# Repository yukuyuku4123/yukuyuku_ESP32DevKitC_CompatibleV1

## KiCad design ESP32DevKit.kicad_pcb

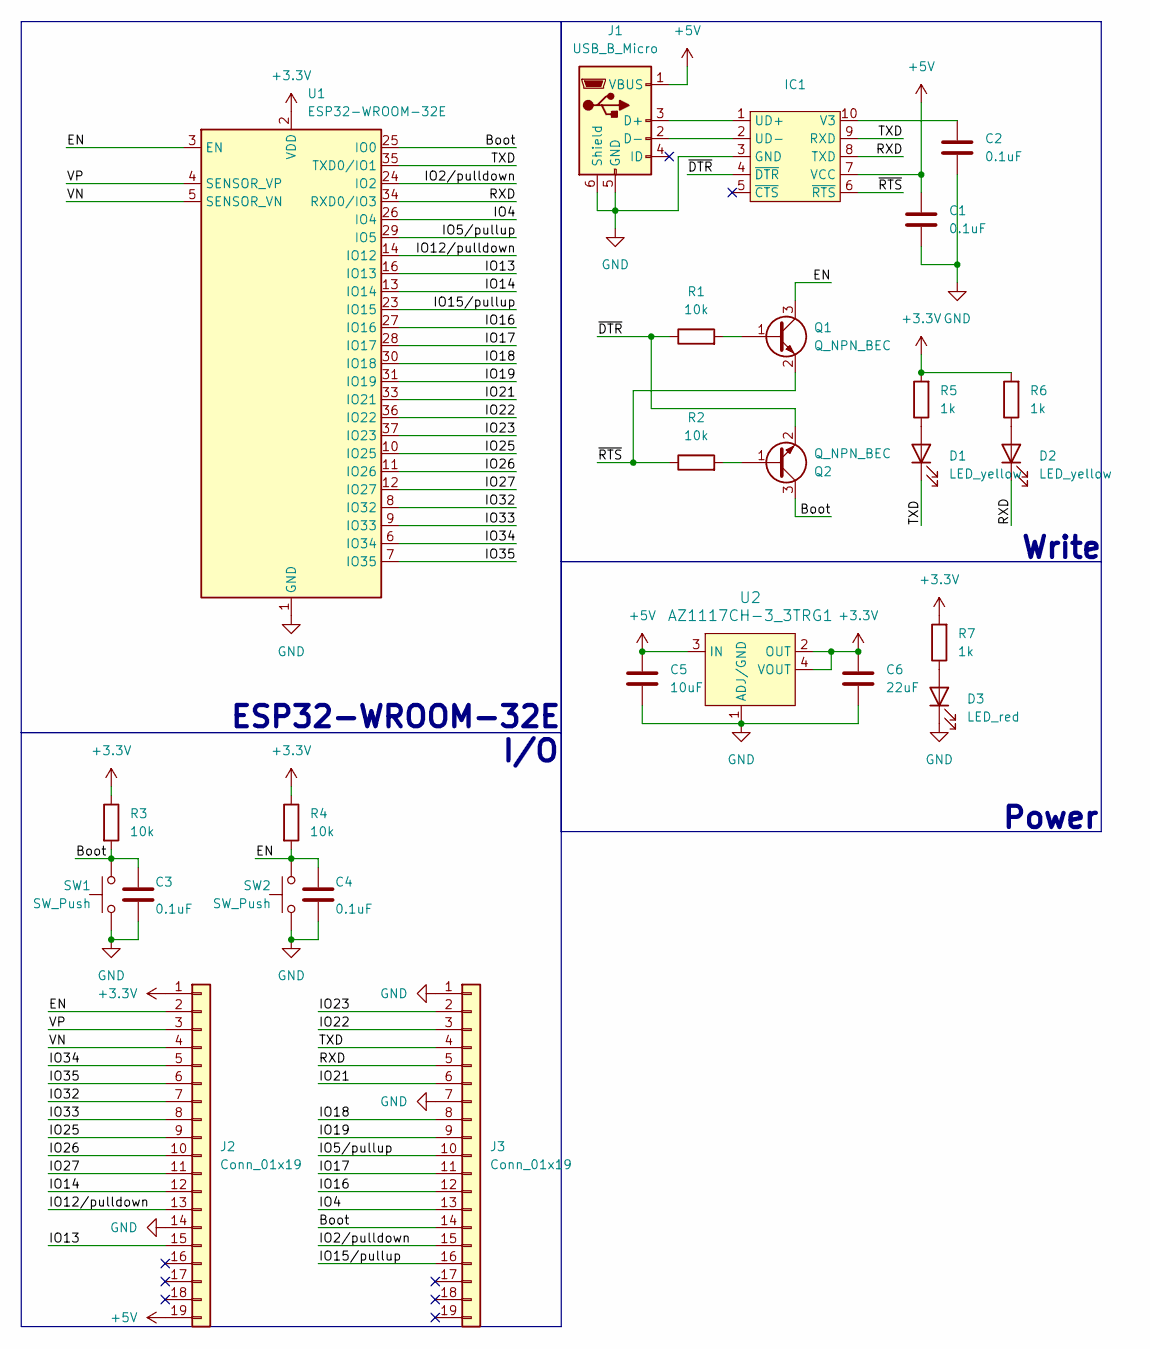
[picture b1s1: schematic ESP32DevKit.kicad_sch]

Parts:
C1, C2, C3, C4: 0.1uF; C_0603_1608Metric
C5: 10uF; C_0603_1608Metric
C6: 22uF; C_0603_1608Metric
D1, D2: LED_yellow; LED_0603_1608Metric
D3: LED_red; LED_0603_1608Metric
IC1: SSOP-10_3.9x4.9mm_P1.00mm
J1: USB_B_Micro; USB_Micro-B_Molex_47346-0001
J2, J3: Conn_01x19; PinHeader_1x19_P2.54mm_Vertical
Q1, Q2: Q_NPN_BEC; SC-59
R1, R2, R3, R4: 10k; R_0603_1608Metric
R5, R6, R7: 1k; R_0603_1608Metric
SW1, SW2: SW_Push; SW_Push_SPST_NO_Alps_SKRK
U1: ESP32-WROOM-32E
U2: AZ1117CH-3_3TRG1; SOT-223; MPN AZ1117CH-3.3TRG1

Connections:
+3.3V: C6.1, J2.1, R3.1, R4.1, R5.2, R6.2, R7.2, U1.2 (VDD), U2.2 (OUT), U2.4 (VOUT)
+5V: C1.1, C5.1, IC1.7 (VCC), J1.1 (VBUS), J2.19, U2.3 (IN)
/Boot: C3.1, J3.14, Q2.3 (C), R3.2, SW1.2, U1.25 (IO0)
/EN: C4.1, J2.2, Q1.3 (C), R4.2, SW2.2, U1.3 (EN)
/IO2/pulldown: J3.15, U1.24 (IO2)
/IO4: J3.13, U1.26 (IO4)
/IO5/pullup: J3.10, U1.29 (IO5)
/IO12/pulldown: J2.13, U1.14 (IO12)
/IO13: J2.15, U1.16 (IO13)
/IO14: J2.12, U1.13 (IO14)
/IO15/pullup: J3.16, U1.23 (IO15)
/IO16: J3.12, U1.27 (IO16)
/IO17: J3.11, U1.28 (IO17)
/IO18: J3.8, U1.30 (IO18)
/IO19: J3.9, U1.31 (IO19)
/IO21: J3.6, U1.33 (IO21)
/IO22: J3.3, U1.36 (IO22)
/IO23: J3.2, U1.37 (IO23)
/IO25: J2.9, U1.10 (IO25)
/IO26: J2.10, U1.11 (IO26)
/IO27: J2.11, U1.12 (IO27)
/IO32: J2.7, U1.8 (IO32)
/IO33: J2.8, U1.9 (IO33)
/IO34: J2.5, U1.6 (IO34)
/IO35: J2.6, U1.7 (IO35)
/RXD: D2.1 (K), IC1.8 (TXD), J3.5, U1.34 (RXD0/IO3)
/TXD: D1.1 (K), IC1.9 (RXD), J3.4, U1.35 (TXD0/IO1)
/VN: J2.4, U1.5 (SENSOR_VN)
/VP: J2.3, U1.4 (SENSOR_VP)
/~DTR: IC1.4 (~DTR), Q2.2 (E), R1.1
/~RTS: IC1.6 (~RTS), Q1.2 (E), R2.1
GND: C1.2, C2.2, C3.2, C4.2, C5.2, C6.2, D3.1 (K), IC1.3 (GND), J1.5 (GND), J1.6 (Shield), J2.14, J3.1, J3.7, SW1.1, SW2.1, U1.1 (GND), U1.15 (GND), U1.38 (GND), U1.39 (GND), U2.1 (ADJ/GND)
unnamed: D1.2 (A), R5.1
unnamed: D2.2 (A), R6.1
unnamed: D3.2 (A), R7.1
unnamed: IC1.1 (UD+), J1.3 (D+)
unnamed: IC1.2 (UD-), J1.2 (D-)
unnamed: C2.1, IC1.10 (V3)
unnamed: Q1.1 (B), R1.2
unnamed: Q2.1 (B), R2.2

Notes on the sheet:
I/O
ESP32-WROOM-32E
Power
Write

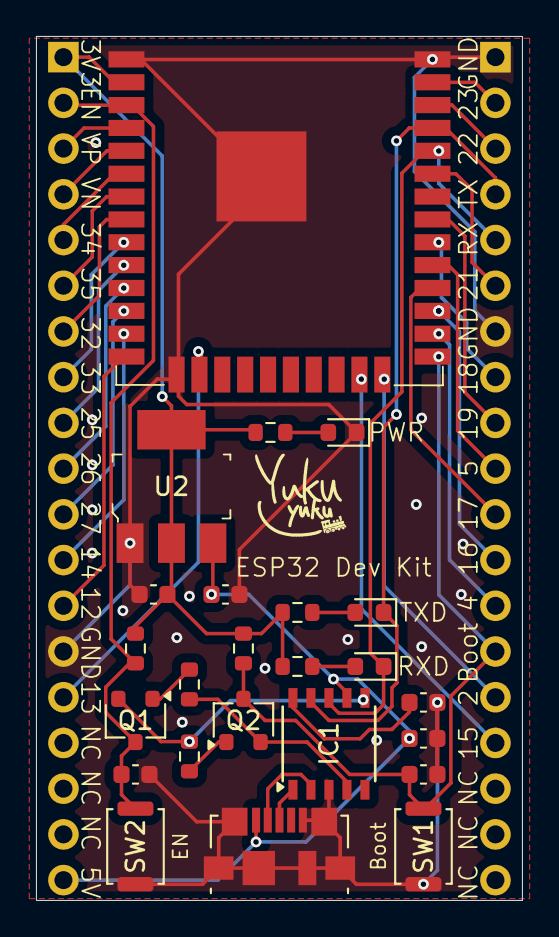
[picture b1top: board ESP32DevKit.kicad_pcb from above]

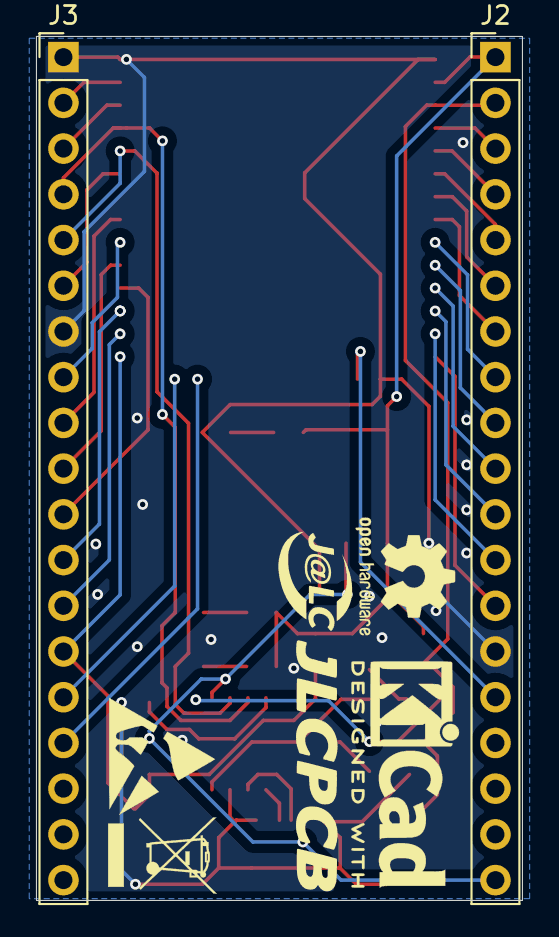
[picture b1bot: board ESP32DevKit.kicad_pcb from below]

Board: 2 copper layers, 27.0 x 48.0 mm, 26 parts (2 on the bottom side), 40 nets.

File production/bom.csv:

Designator,Footprint,Quantity,Value,LCSC Part #
"C1, C2, C3, C4",0603,4,0.1uF,
C5,0603,1,10uF,
C6,0603,1,22uF,
"D1, D2",0603,2,LED_yellow,
D3,0603,1,LED_red,
IC1,TSSOP-10_3x3mm_P0.5mm,1,~,
J1,USB_Micro-B_Molex_47346-0001,1,USB_B_Micro,
"J2, J3",PinHeader_1x19_P2.54mm_Vertical,2,Conn_01x19,
"Q1, Q2",SC-59,2,Q_NPN_BEC,
"R1, R2, R3, R4",0603,4,10k,
"R5, R6, R7",0603,3,1k,
"SW1, SW2",SW_Push_SPST_NO_Alps_SKRK,2,SW_Push,
U1,ESP32-WROOM-32E,1,ESP32-WROOM-32E,
U2,SOT-223,1,AZ1117CH-3_3TRG1,AZ1117CH-3.3TRG1

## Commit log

2024-07-27 Ver-1.0
2024-07-27 Create LICENSE
2024-07-27 Update LICENSE
